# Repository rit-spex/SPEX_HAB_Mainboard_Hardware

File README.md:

# SPEX_HAB_Mainboard_Hardware

Mainboard for RIT SPEX's High Altitude Balloon Program. 
This board is part of a modular system that allows for quick reuse and testing of future cubesat payloads.

Hardware on board includes:
- Altimeter
- 9DOF IMU
- Temperature Sensor
- Three external Thermistors
- Onboard MicroSD Storage 
- MOSFETs for multiple voltages
- Full Dataline ESD Protection

</img> </img> </img> 
</img> 

</img> </img> </img> 

</img>

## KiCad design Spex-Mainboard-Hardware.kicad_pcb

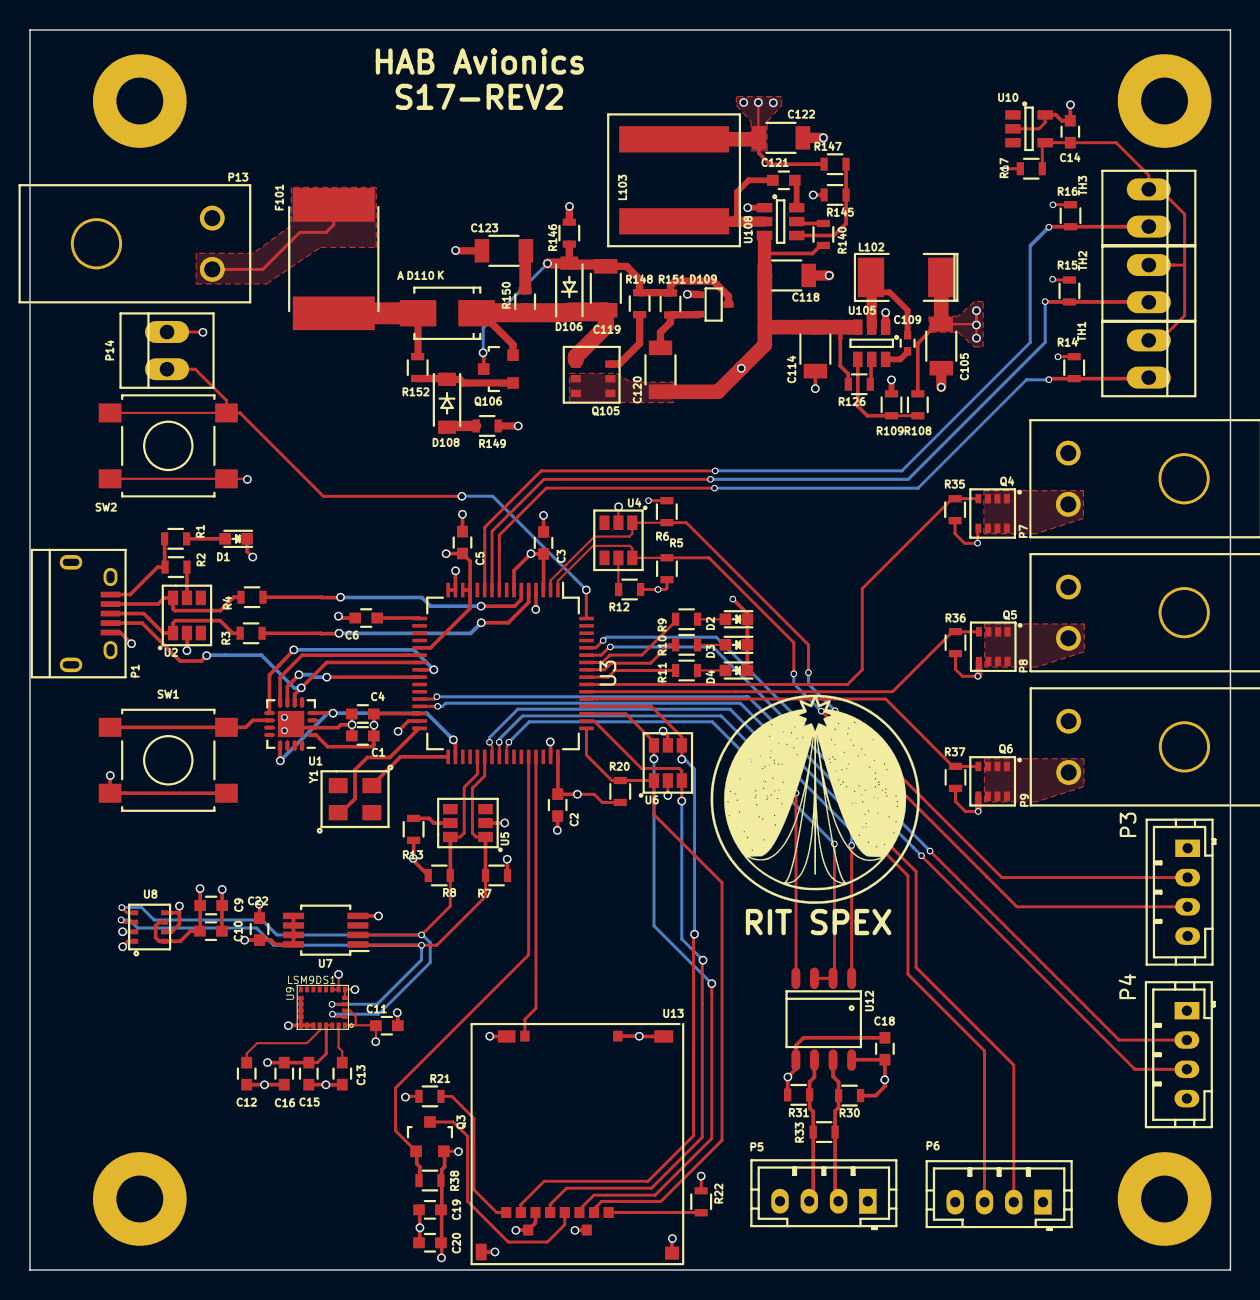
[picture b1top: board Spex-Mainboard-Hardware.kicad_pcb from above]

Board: 4 copper layers, 82.0 x 84.7 mm, 113 parts (0 on the bottom side), 80 nets.

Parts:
C1, C2, C3, C4, C18, C22: 1uF; C_0603
C5: 2.2uF; C_0603
C6, C19: .1uF; C_0603
C9, C10, C11, C13, C15: 100nF; C_0603
C12: 10nF; C_0603
C14: 4.7uF; C_0603
C16, C20: 10uF; C_0603
C105, C122: 47uf; C_1206
C109: 100nf; C_0402
C114, C118: 22uf; C_1206
C119, C123: 1uf 100v; C_1206
C120: .1uf 100v; C_1206
C121: 100nf; C_0603
D1, D2, D3, D4: LED; LED_0603
D106, D108: ZENER; SOD-123
D109: D_Schottky_x2_Serial_AKC; SC-70
D110: DIODE; SMA_Standard
F101: FUSE; Fuse_SMD2920
L102: 2.2uh; SMD-2010_Pol
L103: 3.3uh; NRS8030T3R3MJGJ
P1: USB_OTG; USB_Micro-B
P3, P4, P5, P6: CONN_01X04; JST_PH_B4B-PH-K_04x2.00mm_Straight
P7, P8, P9, P13: CONN_01X02; ultraFitCONN_2
P14: CONN_01X02; PINHEAD1-2
Q3: BSS215PH6327; SOT-23
Q4, Q5, Q6: Si5468DC; ChipFet-8
Q105: Si3407DV
Q106: Q_PNP_BEC; SOT-23
R1, R9, R10, R11: 1K; R_0603
R2, R12, R20, R38, R126, R140: 10K; R_0603
R3, R4: 33; R_0603
R5, R6, R7, R8: 4.7K; R_0603
R13, R30, R31, R35, R36, R37, R109, R145: 10k; R_0603
R14, R15, R16: 12k; R_0603
R17: 240; R_0603
R21, R22: 51K; R_0603
R33: 120; R_0603
R108, R146: 33.2k; R_0603
R147: 56.2k; R_0603
R148, R150: 10; R_0603
R149: 27.4k; R_0603
R151: 10.2k; R_0603
R152: 100k; R_0603
SW1, SW2: SW_PUSH; SW_SPST_B3S-1000
TH1, TH2, TH3: THERMISTOR; PINHEAD1-2
U1: MKL02Z32VFG4; QFN-16-1EP_3x3mm_Pitch0.5mm
U2, U4, U5: NUP2201MR6; TSOP-6
U3: MK20DX256VLH7; LQFP-64_10x10mm_Pitch0.5mm
U6: MMQA6V2T1G; TSOP-6
U7: MCP9808T; MSOP-8_3x3mm_Pitch0.65mm
U8: BME280; LGA-8
U9: LSM9DS1; LGA-24
U10: LM4030; SOT-23-5
U12: ST1480ABDR; SO-8
U13: SCHA4B0419; SCH4B0419
U105, U108: TPS563200; SOT-23-6
Y1: Crystal; CX3225GB16000D0HPQCC

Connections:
3.3V_MOS_CTRL: Q4.4, R35.2, U3.55
5V_MOS_CTRL: Q5.4, R36.2, U3.54
+3V3: C1.1, C2.1, C3.1, C4.1, C5.1, C9.1, C10.1, C11.1, C15.1, C16.1, C18.1, C19.1, C20.1, C22.1, C105.1, L102.1, P3.1, P4.1, P5.1, P6.1, P7.2, Q3.2, R5.2, R6.2, R7.2, R8.2, R12.1, R13.1, R17.1, R20.1, R21.1, R22.2, R30.1, R38.2, R108.1, U1.1, U3.3, U3.7, U3.13, U3.14, U3.21, U3.30, U3.48, U7.5, U7.6, U7.7, U7.8, U8.2, U8.6, U8.8, U9.1, U9.3, U9.7, U9.8, U9.22, U9.23, U12.8
+5V: C122.1, L103.1, P8.2, R147.1
/Data_Input_Output/3.3V_MOS_OUT: P7.1, Q4.1, Q4.2, Q4.3, Q4.6, Q4.7, Q4.8
/Data_Input_Output/5V_MOS_OUT: P8.1, Q5.1, Q5.2, Q5.3, Q5.6, Q5.7, Q5.8
/Data_Input_Output/RS485_A: P5.3, R31.1, R33.2, U12.6
/Data_Input_Output/RS485_B: P5.2, R30.2, R33.1, U12.7
/Data_Input_Output/Vbus_MOS_OUT: P9.1, Q6.1, Q6.2, Q6.3, Q6.6, Q6.7, Q6.8
/HAB Sensors/2.5VRefVoltage: C14.1, R17.2, TH1.1, TH2.1, TH3.1, U10.4
/PTA6: P1.4, U1.6, U3.23
/PTA7: U1.7, U3.25
/PTB0: U1.8, U3.22
/PTB1: U1.9, U3.24
/PTB2: SW1.1, U1.10
/Power Distribution/VBat: F101.1, P13.2
/Toggle: P14.1, SW2.1, U3.64
GND: C1.2, C2.2, C3.2, C4.2, C5.2, C6.2, C9.2, C10.2, C11.2, C12.2, C13.2, C14.2, C15.2, C16.2, C18.2, C19.2, C20.2, C22.2, C105.2, C114.1, C118.1, C122.2, C123.2, D1.1, D2.1, D3.1, D4.1, D109.1, P1.5, P1.6, P3.4, P4.4, P5.4, P6.4, P13.1, P14.2, Q4.5, Q5.5, Q6.5, R14.2, R15.2, R16.2, R31.2, R35.1, R36.1, R37.1, R109.2, R145.2, R146.2, R149.2, SW1.2, SW2.2, U1.2, U2.2, U3.4, U3.15, U3.16, U3.31, U3.47, U4.2, U5.2, U6.2, U6.5, U7.4, U8.1, U8.5, U8.7, U9.5, U9.6, U9.14, U9.15, U9.16, U9.17, U9.18, U9.19, U9.20, U10.2, U10.5, U12.5, U13.6, U13.10, U105.1, U108.1
I2C0_SCL: R8.1, U3.37, U5.6, U7.2, U8.4, U9.2
I2C0_SDA: R7.1, U3.38, U5.1, U7.1, U8.3, U9.4
I2C1_SCL: P3.2, R6.1, U3.2, U4.1
I2C1_SDA: P3.3, R5.1, U3.1, U4.6
I/O-1: P6.2, U3.28
I/O-2: P6.3, U3.29
LED_Heartbeat: R9.1, U3.58
LED_Status_1: R10.1, U3.57
LED_Status_2: R11.1, U3.56
unnamed: C6.1, U3.17
unnamed: C12.1, U9.21
unnamed: C13.1, U9.24
unnamed: C109.1, L102.2, U105.2
unnamed: C109.2, U105.6
unnamed: C119.1, D106.1, D110.1, Q105.4, Q106.2, R150.1
unnamed: C119.2, D106.2, D109.3, Q106.3, R146.1, R148.2, R151.2
unnamed: C120.2, D109.2, R151.1
unnamed: C121.1, L103.2, U108.2
unnamed: C121.2, U108.6
unnamed: C123.1, R150.2
unnamed: D1.2, R1.2
unnamed: D2.2, R9.2
unnamed: D3.2, R10.2
unnamed: D4.2, R11.2
unnamed: D108.1, Q106.1, R152.1
unnamed: D108.2, R149.1
unnamed: D110.2, F101.2, R152.2
unnamed: P1.1, R1.1, R2.2
unnamed: P1.2, R4.2, U2.6
unnamed: P1.3, R3.2, U2.1
unnamed: Q3.3, U13.4
unnamed: Q105.3, R148.1
unnamed: R2.1, U2.5
unnamed: R3.1, U3.5
unnamed: R4.1, U3.6
unnamed: R12.2, U4.5
unnamed: R13.2, U5.5
unnamed: R21.2, U13.8
unnamed: R22.1, U13.1
unnamed: R108.2, R109.1, U105.4
unnamed: R126.1, U105.5
unnamed: R140.1, U108.5
unnamed: R145.1, R147.2, U108.4
unnamed: U3.32, Y1.1
unnamed: U3.33, Y1.2
RESET_b: U1.4, U1.13, U3.34
RX/TX_CTRL: U3.41, U12.2, U12.3
SD_CTRL: Q3.1, R38.1, U3.44
SD_Detect: U3.45, U13.9
SPI0_CS0: R20.2, U3.49, U6.1, U13.2
SPI0_MISO: U3.52, U6.4, U13.7
SPI0_MOSI: U3.51, U6.6, U13.3
SPI0_SCK: U3.50, U6.3, U13.5
Temp1: R14.1, TH1.2, U3.9
Temp2: R15.1, TH2.2, U3.10
Temp3: R16.1, TH3.2, U3.11
UART0_RX: U3.39, U12.1
UART0_TX: U3.40, U12.4
UART2_RX: P4.3, U3.59
UART2_TX: P4.2, U3.60
Vbus: C114.2, C118.2, C120.1, P9.2, Q105.1, Q105.2, Q105.5, Q105.6, R126.2, R140.2, U105.3, U108.3
Vbus_MOS_CTRL: Q6.4, R37.2, U3.53

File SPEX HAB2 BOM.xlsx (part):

Bill of Materials (BOM) - RIT High Altitude Balloon Test 1 (HAB1)
> All parts seperated by color, GREEN for Mainboard, BLUE for Balloon board.
Item # | Qty | Ref Des | Manufacturer | Mfg Part # | Dist. Part # | Price Per Unit | Total Price | Description | Package | Type | Datasheet |  |  |  |  |  | Notes
1 | 1 | U1 | PJRC | MKL02z32VFG4 |  | 6.8 | 6.8 | Secondary Microcontroller/Bootloader | QFN-16 | SMD | http://www.pjrc.com/store/ic_mkl02.html
2 | 3 | U2,U4,U5 | ON Semicondutor | NUP2201MR6T1G | 863-NUP2201MR6T1G | 0.55000000000000004 | 1.6500000000000001 | ESD Protection 2 lines | TSOP-6 | SMD
3 | 1 | U3 | NXP / Freescale | MK20DX256VLH7 | 841-MK20DX256VLH7 | 7.07 | 7.07 | Primary Microcontroller | LQFP-64 | SMD
4 | 1 | U6 | ON Semicondutor | MMQA6V2T1G | 863-MMQA6V2T1G | 0.48 | 0.48 | ESD Protection 4 lines | TSOP-6 | SMD
5 | 1 | U7 | Microchip Technology | MCP9808T-E/MS | 579-MCP9808T-E/MS | 1.22 | 1.22 | Temperature Sensor | MSOP-8 | SMD
6 | 1 | U8 | Bosch Sensortec | BME280 | 262-BME280 | 5.66 | 5.66 | Altimeter (pressure temperature) | LGA-8 | SMD
7 | 1 | U9 | STMicroelectronics | LSM9DS1TR | 511-LSM9DS1TR | 6.21 | 6.21 | 9DOF IMU (accel, gyro, compass) | LGA-24 | SMD
8 | 1 | U10 | Texas Instruments | LM4030BMF-2.5/NOPB | 926-LM4030BMF25NOPB | 2.12 | 2.12 | 2.5V precision voltage reference | SOT23-6 | SMD
10 | 1 | U12 | STMicroelectronics | ST1480ABDR | 511-ST1480ABDR | 1.4 | 1.4 | RS485 Transceiver | SO-8 | SMD
11 | 1 | U13 | ALPS | SCHA4B0419 | 688-SCHA4B0419 | 0.8 | 0.8 | MicroSD card slot |  | SMD
13 | 2 | U105,U108 | Texas Instruments | TPS563200DDCR | 595-TPS563200DDCR | 1.45 | 2.9 | 3.3V/5V Power Regulator | SOT-23-6 | SMD
14 | 1 | Y1 | AVX | CX3225GB16000D0HPQCC | 581-CX3225GB16DHPQCC | 0.72 | 0.72 | 16mhz cyrstal |  | SMD
 |  | SW1 | CTS Electronic Components | 222AMVBAR | 774-222AMVBAR | 0.42 | 0 | reset button | Gull Wing | SMD
15 | 2 | SW2 |  |  |  | 0.42 | 0.84 |  |  | SMD
16 | 3 | TH1,TH2,TH3 | Vishay / BC Components | NTCLE100E3103JB0 | 594-2381-640-63103 | 0.26 | 0.78 | Thermistor | BULK | Thru Hole
19 | 1 | Q3 | Infineon Technologies | BSS215P H6327 | 726-BSS215PH6327XT | 0.46 | 0.46 | P channel mosfet |  | SMD
20 | 3 | Q4,Q5,Q6 | Vishay Semiconductors | Si5468DC-T1-GE3 | 781-SI5468DC-GE3 | 0.52 | 1.56 | N channel power mosfet |  | SMD
22 | 1 | Q105 | Vishay Semiconductors | SI3407DV-T1-GE3 | 781-SI3407DV-GE3 | 0.52 | 0.52 | N channel power mosfet |  | SMD
23 | 1 | Q106 | ON Semicondutor | MMBT3906LT1G | 863-MMBT3906LT1G | 0.1 | 0.1 | BJT Transistor | SOT-23 | SMD | http://www.mouser.com/ds/2/308/MMBT3906LT1-D-112192.pdf
24 | 1 | D1 | Kingbright | AP1608SGC | 604-AP1608SGC | 0.13 | 0.13 | Green LED | 0603 | SMD | http://www.mouser.com/ds/2/216/AP1608SGC-29521.pdf
25 | 1 | D2 | OSRAM Opto | LB Q39G-L2OO-35-1 | 720-LBQ39GL2N2351 | 0.15 | 0.15 | Blue LED | 0603 | SMD
26 | 1 | D3,D4 | OSRAM Opto | LS Q976-NR-1 | 720-LSQ976-NR-1 | 0.1 | 0.1 | Red LED | 0603 | SMD | http://www.mouser.com/ds/2/311/LS%20Q976%20-%20CHIPLED%20060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
29 | 2 | D106,D108 | Diodes Incorportated | BZT52C16-7-F | 621-BZT52C16-F | 0.19 | 0.38 |  |  | SMD
30 | 1 | D109 | ON Semicondutor | BAV99WT1G | 863-BAV99WT1G | 0 | 0 |  |  | SMD
31 | 1 | L102 | Laird Technologies | TYS50402R2N-10 | 875-TYS50402R2N-10 | 0.38 | 0.38 | 2.2uH Inductor |  | SMD
32 | 1 | L103 | Taiyo Yuden | NRS8030T3R3MJGJ | 963-NRS8030T3R3MJGJ | 0.48 | 0.48 | 3.3uH Inductor | 8030 | SMD
33 | 1 | D110 | Diodes Incorportated | B340-13-F | 621-B340-F | 0.34 | 0.34 | input diode |  | SMD
34 | 1 | F101 | Bourns | MF-LSMF260X-2 | 652-MF-LSMF260X-2 | 0.46 | 0.46 | Resetable fuse | 3121 | SMD
36 | 1 | P1 | JAE Electronics | DX4R005JJ6R1500 | 656-DX4R005JJ6R1500 | 0.97 | 0.97 | MicroB USB connector |  | Thru Hole
38 | 4 | P3,P4,P5,P6 | JST (Sparkfun) |  | PRT-09916 | 1.5 | 6 | JST PH 4 pin (full assembly) | CONN | Thru Hole | https://www.sparkfun.com/products/9916
39 | 7 | P7,P8,P9,P10,P11,P12,P13 | Molex | 172310-1102 | 538-172310-1102 | 0.72 | 5.04 | UltraFit 2pin Header(male) | CONN | Thru Hole
40 | 4 | R1,R9,R10,R11 | Panasonic | ERJ-3EKF1001V | 667-ERJ-3EKF1001V | 0.1 | 0.4 | 1k ohm resistor | 0603 | SMD | http://www.mouser.com/ds/2/315/AOA0000CE2-37512.pdf |  |  |  |  |  | order 100
41 | 14 | R2,R12,R13,R20,R30,R31,R35,R36,R37,R38,R109,R126,R130,R140,R145 | Panasonic | ERJ-3GEYJ103V | 667-ERJ-3GEYJ103V | 0.1 | 1.4000000000000001 | 10k ohm resistor | 0603 | SMD |  |  |  |  |  |  | order 100
 | 2 | R21,R22 | KOA Speer | RK73B1JTTDD513J | 660-RK73B1JTTDD513J | 0.08 | 0.16 | 51k ohm resistor | 0603 | SMD | http://www.mouser.com/ds/2/219/RK73B-919.pdf
42 | 2 | R3,R4 | Vishay / Dale | CRCW060333R0FKEA | 71-CRCW0603-33-E3 | 0.1 | 0.2 | 33 ohm resistor | 0603 | SMD
43 | 3 | R14,R15,R16 | Susumu | RR0816P-123-D | 754-RR0816P-123D | 0.1 | 0.30000000000000004 | 12k ohm resistor (0.5%) | 0603 | SMD | http://www.mouser.com/ds/2/392/susumu_RR_Data_Sheet-358748.pdf
44 | 1 | R17 | KOA Speer | RK73B1JTTDD241J | 660-RK73B1JTTDD241J | 0.08 | 0.08 | 240 ohm resistor | 0603 | SMD | http://www.mouser.com/ds/2/219/RK73B-919.pdf
45 | 5 | R5,R6,R7,R8,R28 | Panasonic | ERJ-3EKF4701V | 667-ERJ-3EKF4701V | 0.1 | 0.5 | 4.7k ohm resistor | 0603 | SMD | http://www.mouser.com/ds/2/315/AOA0000CE2-37512.pdf |  |  |  |  |  | order 100
46 | 1 | R33 | KOA Speer | RK73B1JTTDD121J | 660-RK73B1JTTDD121J | 0.08 | 0.08 | 120 ohm resistor | 0603 | SMD | http://www.mouser.com/ds/2/219/RK73B-919.pdf
47 | 2 | R108,R146 | Panasonic | ERJ-3EKF3322V | 667-ERJ-3EKF3322V | 0.1 | 0.2 | 33.2k ohm resistor | 0603 | SMD | http://www.mouser.com/ds/2/427/dcrcwe3-109170.pdf
48 | 1 | R147 | Panasonic | ERJ-3EKF5622V | 667-ERJ-3EKF5622V | 0.1 | 0.1 | 56.2k ohm resistor | 0603 | SMD | http://www.mouser.com/ds/2/315/AOA0000CE2-37512.pdf
49 | 2 | R148, R150 | Panasonic | ERJ-3EKF10R0V | 667-ERJ-3EKF10R0V | 0.1 | 0.2 | 10 ohm resistor | 0603 | SMD | http://www.mouser.com/ds/2/315/AOA0000CE2-37512.pdf
50 | 1 | R149 | Bourns | CR0603-FX-2742ELF | 652-CR0603FX-2742ELF | 0.1 | 0.1 | 27.4K ohm resistor | 0603 | SMD | http://www.mouser.com/ds/2/54/hpreztr-777398.pdf
51 | 1 | R151 | Panasonic | ERJ-3EKF1022V | 667-ERJ-3EKF1022V | 0.1 | 0.1 | 10.2k ohm resistor | 0603 | SMD | http://www.mouser.com/ds/2/315/AOA0000CE2-37512.pdf
52 | 1 | R152 | Vishay | RCA0603100KJNEC | 71-RCA0603100KJNEC | 0.09 | 0.09 | 100k ohm resistor | 0603 | SMD | http://www.mouser.com/ds/2/427/rcae3-515375.pdf
53 | 8 | C1,C2,C3,C4,C18,C21,C2 | Wurth Electronics | 885012106017 | 710-885012106017 | 0.08 | 0.64 | 1uF capacitor | 0603 | SMD
54 | 1 | C5 | Yageo | CC0603MRX5R5BB225 | 603-CC603MRX5R5BB225 | 0.1 | 0.1 | 2.2uF capacitor | 0603 | SMD | http://www.mouser.com/ds/2/447/UPY-GPHC_X5R_4V-to-50V_14_071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
55 | 8 | C6,C9,C10,C11,C13,C15,C19,C121 | Wurth Electronics | 885012206071 | 710-885012206071 | 0.04 | 0.32 | 100nF capacitor (0.1uf) | 0603 | SMD
56 | 1 | C109 | Wurth Electronics | 885012105016 | 710-885012105016 | 0.02 | 0.02 | 100nF capacitor | 0402 | SMD | http://www.mouser.com/ds/2/445/885012105016-611018.pdf
57 | 1 | C12 | Wurth Electronics | 885012206040 | 710-885012206040 | 0.04 | 0.04 | 10nF capacitor (0.01uf) | 0603 | SMD | http://www.mouser.com/ds/2/445/885012206040-555095.pdf
58 | 1 | C14 | Yageo | CC0603KRX5R5BB475 | 603-CC603KRX5R5BB475 | 0.11 | 0.11 | 4.7uF capacitor | 0603 | SMD
59 | 2 | C16,C20 | Murata Electronics | GRM188R61A106KE69D | 81-GRM188R61A106KE9D | 0.2 | 0.4 | 10uF capacitor | 0603 | SMD | http://www.murata.com/products/catalog/pdf/c02e.pdf
60 | 2 | C105,C122 | Yageo | CC1206MKX5R5BB476 | 603-CC126MKX5R5BB476 | 0.5 | 1 | 47uF capacitor | 1206 | SMD
61 | 2 | C114,C118 | Murata Electronics | GRM31CR61E226ME15L | 81-GRM31CR61E226ME5L | 0.5 | 1 | 22uF capacitor | 1206 | SMD | http://www.murata.com/products/catalog/pdf/c02e.pdf
62 | 2 | C119, C123 | Taiyo Yuden | HMK316B7105KL-T | 963-HMK316B7105KL-T | 0.43 | 0.86 | 1uF capacitor (100V) | 1206 | SMD
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
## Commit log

2016-03-24 Initial upload to SPEX HAB repo
2016-03-24 added add'l temperature sensor
2016-03-24 updated SD card, changed mosfets
2016-03-24 added components
2016-03-24 updated component numbering
2016-03-24 updated schematic
2016-04-01 Schematics updated/components generated/PCB started
2016-04-01 Added power board to both sch and pcb. Will route when ready for it
2016-04-04 working on PCB layout
2016-04-04 updated parts
2016-04-04 board now 80% laid out
2016-04-04 project updated
2016-04-04 schematic updated
2016-04-04 adding images
2016-04-05 updated schematic, added headers
2016-04-05 continued PCB layout, small schematic changes
2016-04-06 Added powerz
2016-04-06 Routed a line.
2016-04-08 updated board
2016-04-08 board layout 95% complete
2016-04-08 completed first revision of the board.
2016-04-09 added images, cosmetic schematic changes
2016-04-09 added BOM
2016-04-09 updated passive values
2016-04-11 updated BOM
2016-04-11 updated BOM, fixed footprints
2016-04-12 updated gerbers
2016-04-12 added image
2016-04-12 updated PCB
2016-04-25 power estimate
2016-04-27 Added Mainboard Software v0.1
    -Successfully blinks heartbeat
    -raises Relay 17 to HIGH after 15s
2016-04-27 Added data sheets for sensors and started Arduion Project
2016-04-28 Deploys Relay and Reads onboard Barometer
2016-05-05 Comments and code cleanup
    -removed startTimer
    --deprecated by elapsedMillis
2016-05-07 Attribution
2016-05-07 ImagineRIT LED Light Show
    Flashing LEDs for demonstration purposes
2016-06-06 creating revision 1 backup
2016-08-10 rev 2 of hab board in progress
2016-08-24 routing power, digital portion mostly complete
2016-08-24 continued work on power electronics
2016-08-24 the routing never ends
2016-08-24 finished routing all but output MOSFETS
2016-09-16 updates per week 1 meeting
2016-10-14 added images
2016-10-18 small update
    getting ready to order PCB's, making sure they are good to go.
2016-10-19 small update round 2
    cleaning up PCB, adding SPI CS pullup resistors
2016-10-24 fixed mounting points
2016-10-24 routed SPI CS pull up resistors
2016-12-19 BOM should be usable again for Rev2
2016-12-19 small tweaks, BOM updated
2016-12-19 Continued tweaks, updated BOM again
2017-01-30 removed SPI Flash, minor changes, updated Kicad
2017-02-02 Redid the entire lower part of the board (sensors/SD)
    I probably have spent too much time on this board, looks better now
    though
2017-02-02 RTD (read the datasheet)
    keepouts are a thing
2017-02-06 updated image
2017-02-06 minor trace changes and silkscreen improvements
2017-02-06 made it a little bit easier to see where pin 1 goes
2017-02-09 BOM update, silkscreen update
2017-02-10 fixing BOM
2017-03-03 last min fixes to order the board
